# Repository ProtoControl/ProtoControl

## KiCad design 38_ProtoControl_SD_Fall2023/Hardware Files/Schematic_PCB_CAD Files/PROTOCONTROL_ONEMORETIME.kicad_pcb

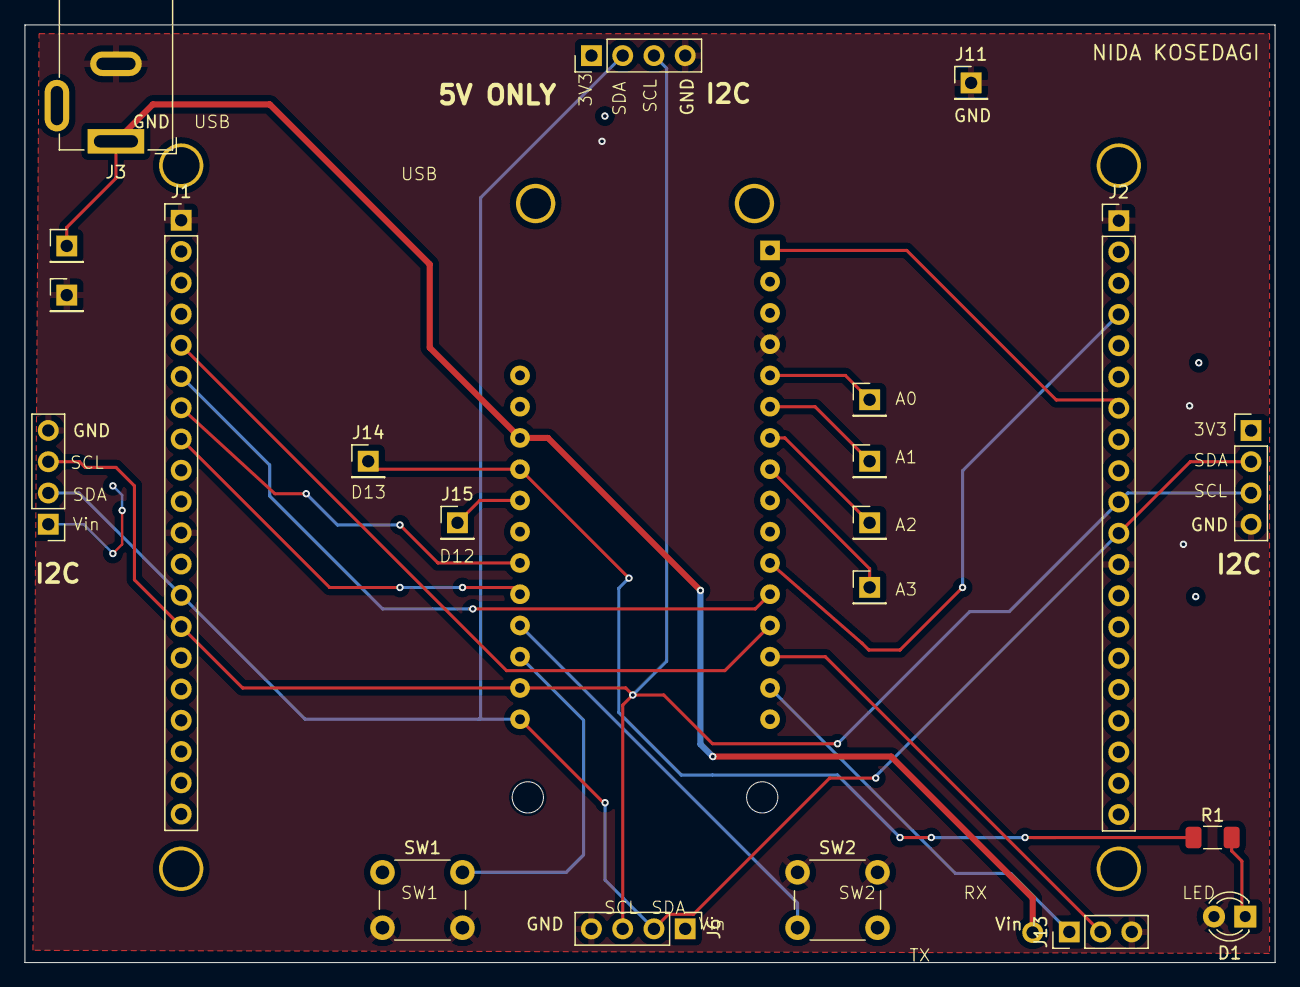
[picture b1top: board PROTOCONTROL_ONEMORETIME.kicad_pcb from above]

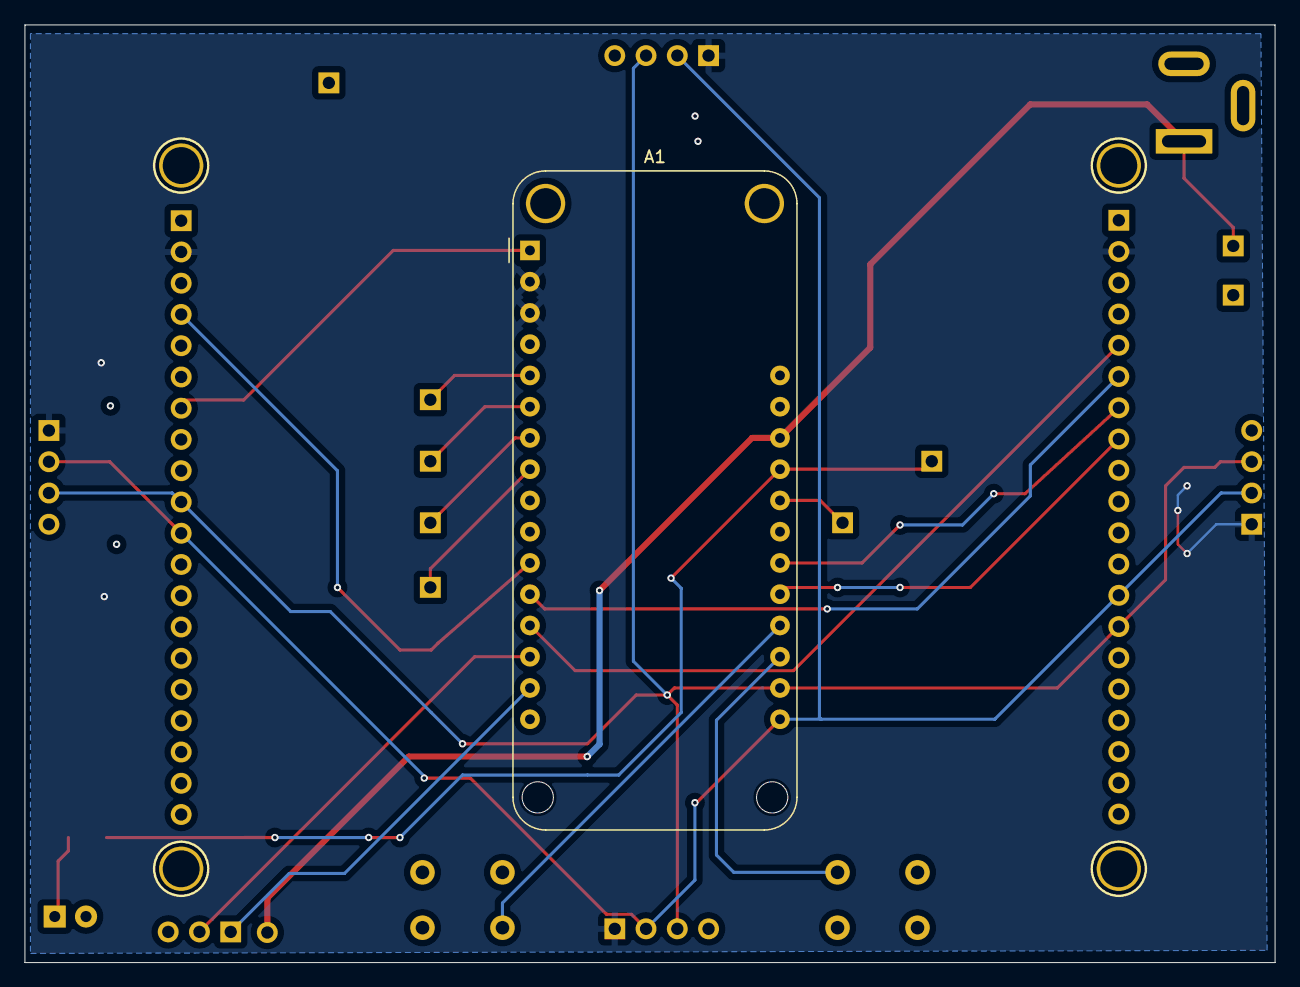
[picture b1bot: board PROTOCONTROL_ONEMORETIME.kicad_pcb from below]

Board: 2 copper layers, 101.6 x 76.2 mm, 26 parts (5 on the bottom side), 20 nets.

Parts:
A1: Adafruit_Feather_M0_Wifi; Adafruit_Feather_M0_Wifi_WithMountingHoles
D1: LED; LED_D3.0mm
J1, J2: Conn_01x20; PinHeader_1x20_P2.54mm_Vertical
J3: Barrel_Jack; BarrelJack_GCT_DCJ200-10-A_Horizontal
J4, J5, J6, J7: Conn_01x04; PinHeader_1x04_P2.54mm_Vertical
J8, J9, J10, J11, J12, J14, J15, J16, J17: Conn_01x01; PinHeader_1x01_P2.54mm_Vertical
J13: Conn_01x03; PinHeader_1x03_P2.54mm_Vertical
R1: 220R; R_1206_3216Metric_Pad1.30x1.75mm_HandSolder
SW1, SW2: SW_Push_Dual; SW_PUSH_6mm
U$7, U$15, U$16, U$17: MOUNTINGHOLE3.0THIN; MOUNTINGHOLE_3.0_PLATEDTHIN

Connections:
3V3: A1.2 (3V3), A1.3 (3V3), J1.2, J2.2, J4.1, J5.1, J6.1, J7.1
A0: A1.5 (DAC0/A0), J8.1
A1: A1.6 (A1), J9.1
A2: A1.7 (A2), J17.1
A3: A1.8 (A3), J16.1
D5: A1.19 (D5), SW1.1
D6: A1.20 (D6), SW2.2
D10: A1.22 (D10), J1.7
D12: A1.24 (D12), J15.1
D13: A1.25 (D13), J14.1, R1.1
D/C: A1.21 (D9), J1.8
GND: A1.4 (GND), D1.2 (A), J1.1, J1.11, J2.1, J2.12, J3.2, J4.4, J5.4, J6.4, J7.4, J11.1, J12.1, J13.3, SW1.2, SW2.1
MISO: A1.13 (MISO/D22), J1.5
MOSI: A1.12 (MOSI/D23), J1.6
unnamed: D1.1 (K), R1.2
RX: A1.14 (RX/D0), J13.2
SCL: A1.18 (SCL/D21), J1.14, J2.10, J4.3, J5.3, J6.3, J7.3
SDA: A1.17 (SDA/D20), J1.13, J2.11, J4.2, J5.2, J6.2, J7.2
TX: A1.15 (TX/D1), J13.1
Vin: A1.26 (VBUS), J3.1, J10.1

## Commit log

2024-04-25 upload
2024-07-06 testing
